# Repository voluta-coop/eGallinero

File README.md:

# eGallinero
El eGallinero es un sistema modular, diseñado para facilitar las tareas que conllevan los cuidados a los animales. En nuestro caso lo hemos enfocado comercialmente a las gallinas para alinearlo con nuestro objeto social, conectar mundo rural y urbano... pero se puede utilizar para multitud de aplicaciones que requieran automatización y monitorización.

¡Reserva el tuyo!

[**RESERVA**](https://www.voluta.coop/taller-iot-competencias-digitales/)  

[**Canal de Telegram**](https://t.me/eGallinero)

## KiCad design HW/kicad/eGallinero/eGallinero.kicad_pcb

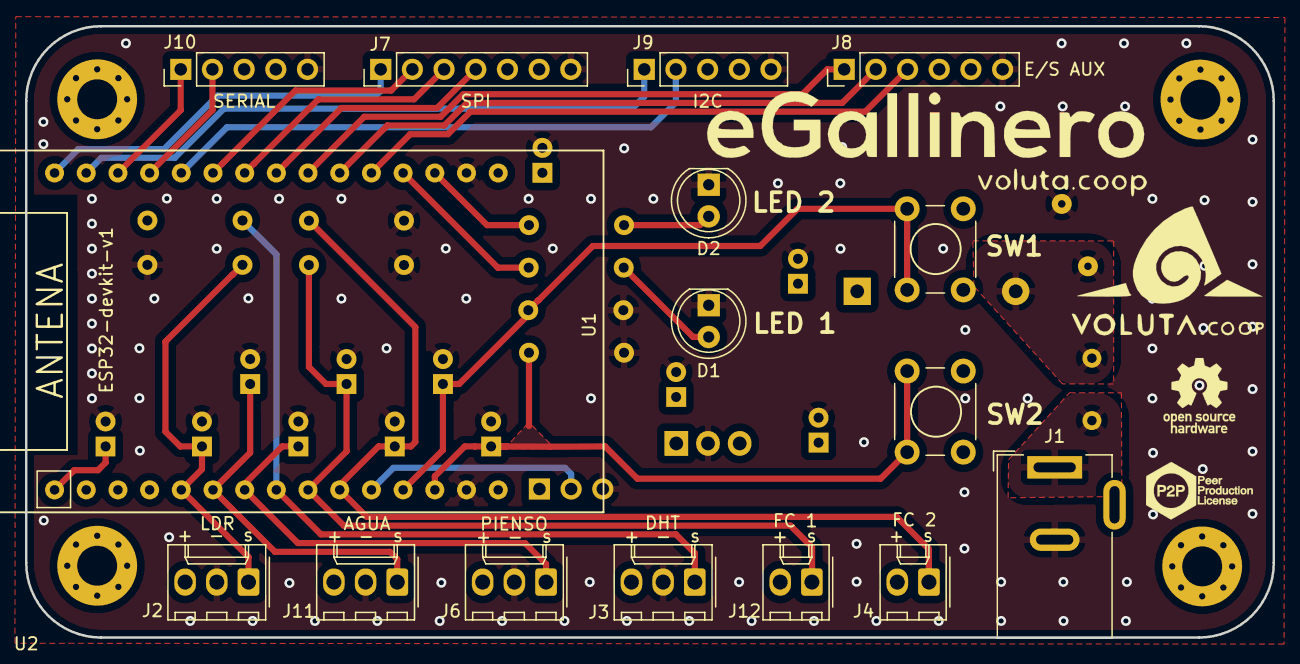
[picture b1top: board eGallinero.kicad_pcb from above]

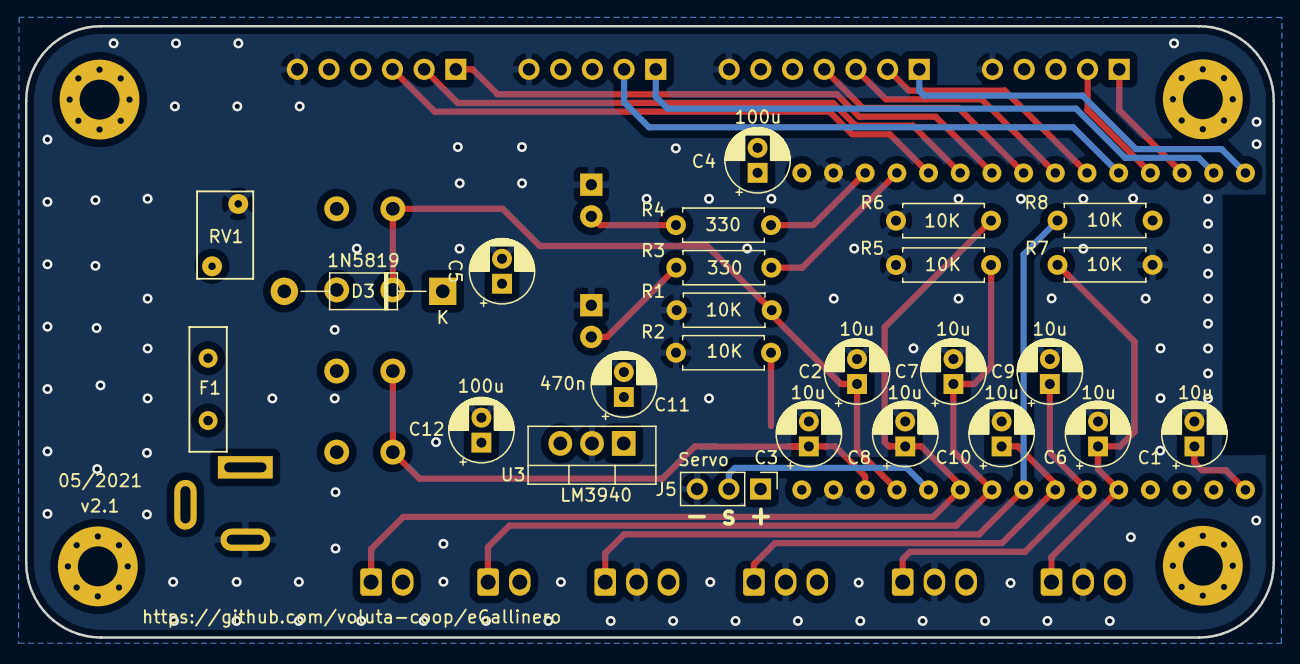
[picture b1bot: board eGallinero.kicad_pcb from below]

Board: 4 copper layers, 100.0 x 49.0 mm, 46 parts (25 on the bottom side), 30 nets.

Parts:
C1, C2, C3, C6, C7, C8, C9, C10: 10u; CP_Radial_D5.0mm_P2.00mm
C4, C5, C12: 100u; CP_Radial_D5.0mm_P2.00mm
C11: 470n; CP_Radial_D5.0mm_P2.00mm
D1: LED 1; LED_D5.0mm_Clear
D2: LED 2; LED_D5.0mm_Clear
D3: 1N5819; D_DO-41_SOD81_P12.70mm_Horizontal
F1: Polyfuse; AHEF100
H1, H2, H3, H4: MountingHole; MountingHole_3.2mm_M3_Pad_Via
J1: Jack-DC; BarrelJack_Wuerth_6941xx301002
J2: LDR; Molex_KK-254_AE-6410-03A_1x03_P2.54mm_Vertical
J3: DHT; Molex_KK-254_AE-6410-03A_1x03_P2.54mm_Vertical
J4: FC 2; Molex_KK-254_AE-6410-02A_1x02_P2.54mm_Vertical
J5: Servo; PinHeader_1x03_P2.54mm_Vertical
J6: PIENSO; Molex_KK-254_AE-6410-03A_1x03_P2.54mm_Vertical
J7: SPI; PinHeader_1x07_P2.54mm_Vertical
J8: E/S AUX; PinHeader_1x06_P2.54mm_Vertical
J9: I2C; PinHeader_1x05_P2.54mm_Vertical
J10: SERIAL; PinHeader_1x05_P2.54mm_Vertical
J11: AGUA; Molex_KK-254_AE-6410-03A_1x03_P2.54mm_Vertical
J12: FC 1; Molex_KK-254_AE-6410-02A_1x02_P2.54mm_Vertical
R1, R2, R5, R6, R7, R8: 10K; R_Axial_DIN0207_L6.3mm_D2.5mm_P7.62mm_Horizontal
R3, R4: 330; R_Axial_DIN0207_L6.3mm_D2.5mm_P7.62mm_Horizontal
RV1: Varistor; RV_Disc_D7mm_W4.5mm_P5mm
SW1, SW2: SW_DIP_x01; SW_PUSH_6mm_H4.3mm
U1: ESP32-devkit-v1; ESP32-DevKit-v1
U2: edge
U3: LM3940; TO-220-3_Vertical

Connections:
+3V3: C4.1, C12.1, J2.3, J3.3, J4.2, J6.3, J7.6, J8.5, J9.4, J10.4, J11.3, J12.2, R8.2, SW1.2, SW2.2, U1.16, U3.3
+5V: C5.1, C11.1, D3.1, J5.1, J7.5, J8.4, J9.3, J10.3, U1.15, U3.1
AGUA: C9.1, J11.1, U1.6
CLK: J7.3, U1.24
CS: J7.4, U1.23
D0: J8.1, U1.22
D1: J8.2, U1.21
D2: J8.3, U1.20
DHT: J3.1, R8.1, U1.8
FC_1: C7.1, J12.1, R5.2, U1.9
FC_2: C8.1, J4.1, R6.2, U1.10
GND: C1.2, C2.2, C3.2, C4.2, C5.2, C6.2, C7.2, C8.2, C9.2, C10.2, C11.2, C12.2, D1.1, D2.1, J1.2, J2.2, J3.2, J5.3, J6.2, J7.7, J8.6, J9.5, J10.5, J11.2, R1.2, R2.2, R5.1, R6.1, R7.2, RV1.2, U1.14, U1.17, U3.2
LDR: C6.1, J2.1, R7.1, U1.5
LED_1: R3.1, U1.19
LED_2: R4.1, U1.18
MISO: J7.2, U1.25
MOSI: J7.1, U1.30
unnamed: C1.1, U1.1
unnamed: D1.2, R3.2
unnamed: D2.2, R4.2
unnamed: D3.2, F1.1, RV1.1
unnamed: F1.2, J1.1
PIENSO: C10.1, J6.1, U1.7
PULS_1: C2.1, R1.1, SW1.1, U1.12
PULS_2: C3.1, R2.1, SW2.1, U1.13
RX: J10.2, U1.27
SCL: J9.1, U1.29
SDA: J9.2, U1.26
SERVO: J5.2, U1.11
TX: J10.1, U1.28

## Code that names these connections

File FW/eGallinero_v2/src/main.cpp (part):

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

// Pines
#define PIN_LED_1 2
#define PIN_LED_2 15
#define PIN_PULSADOR_1 12
#define PIN_PULSADOR_2 13
#define PIN_AGUA 32
#define PIN_PIENSO 33
#define PIN_SERVO 14

// Lectura sensores
#define N_LEC 20 // Número de lecturas para hacer la media de los niveles

// Mensajes Telegram
#define MENSAJE_DIARIO ""
#define MENSAJE_PIENSO "Queda poco pienso."
#define MENSAJE_AGUA "Queda poca agua."

//Estados de configuración

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#define OPERATION_PUERTA 8
#define OPERATION_SENSORES 9

//Constantes Servo
#define PARO 90
#define SUBIR 0
#define BAJAR 180
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int nivel_pienso = 0;


NewPing agua(PIN_AGUA, PIN_AGUA, DIST_MAX_AGUA);
NewPing pienso(PIN_PIENSO, PIN_PIENSO, DIST_MAX_PIENSO);

//Servo
Servo puerta;
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
void outputs(){

    digitalWrite(PIN_LED_1, state_led_1);
    digitalWrite(PIN_LED_2, state_led_2);
    if(state != OPERATION_HORA && state != OPERATION_WIFI) puerta.write(servo);

}
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        

        for(int i = 0; i < N_LEC; i++){
            lec_agua += agua.ping_cm();
            delay(80);
        }
        delay(3000);
        for(int i = 0; i < N_LEC; i++){   
            lec_pienso += pienso.ping_cm();
            delay(80);
        }

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    
    Serial.begin(9600);

    pinMode(PIN_LED_1, OUTPUT);
    pinMode(PIN_LED_2, OUTPUT);
    pinMode(PIN_PULSADOR_1, INPUT);
    pinMode(PIN_PULSADOR_2, INPUT);

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	ESP32PWM::allocateTimer(3);
	puerta.setPeriodHertz(50);    // standard 50 hz servo
    
	puerta.attach(PIN_SERVO, 500, 2400);

    outputs();
}
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
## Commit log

2021-04-15 Se ha subido un .txt con los requisitos.
2021-04-21 Esquema añadido y modificación en requisitos
2021-04-22 .gitignore añadido
2021-04-23 Actualización Readme
2021-04-28 LICENSE
    The peer production license is an example of the Copyfair type of license, in which only other commoners, cooperatives and nonprofits can share and re-use the material, but not commercial entities in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
2021-04-28 Create LICENSE
    Actualización de una licencia
2021-05-07 Capturas del render de la PCB eGallinero v2.1
2021-05-11 Distribución de costes
2021-05-11 Nombre costes
2021-05-27 FW añadido
2021-05-27 Código para debug eliminado
2021-05-28 Actualización costes
2021-06-03 bugs puerta solucionados
2021-06-10 bugs de la puerta solucionados
2021-07-03 Resolución de bugs
2021-07-28 Archivos .stl para imprimir
2021-09-01 Imágenes Kit eGallinero montado
2021-10-08 Corrección de dimensiones
2021-10-08 Eliminación de tapa servo erronea
2021-10-09 Añadido soporte para final de carrera
2022-03-13 Add files via upload
    By Lorena Peydro e Iván Monzón
2022-04-28 eliminar archivo 'control_agua'
